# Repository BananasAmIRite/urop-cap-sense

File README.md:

# All testing code for Capacitive Sensing UROP

## Outline

- `cap_sense_lib/`: Uses the CapacitiveSensor to sense effective capacitance
- `cap_sense_basic/`: Basic Arduino sketch for capacitive sensing experiments. Replicates implementation by cap_sense_lib
- `test_square_wave/`: Testing square wave generation and receiving it using electrodes that are not touching

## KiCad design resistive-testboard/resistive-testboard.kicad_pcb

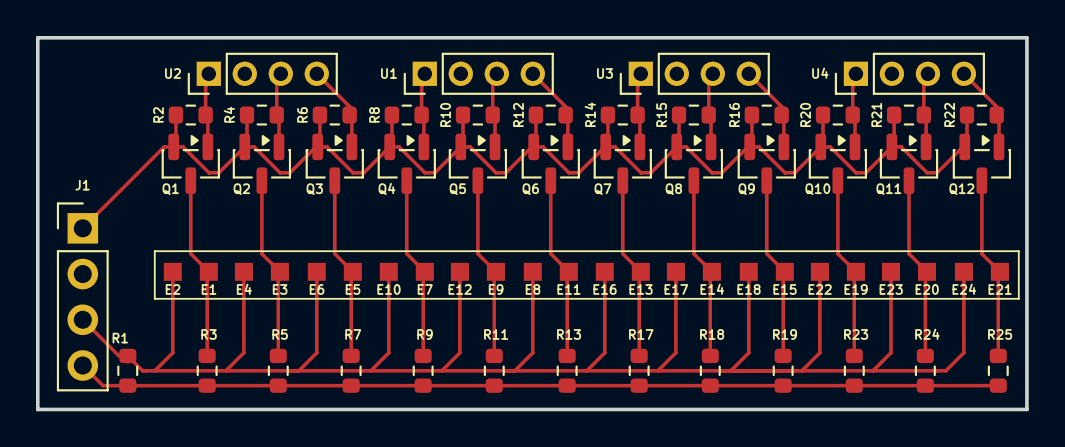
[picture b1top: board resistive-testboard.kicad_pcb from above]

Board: 2 copper layers, 55.0 x 20.6 mm, 66 parts (0 on the bottom side), 27 nets.

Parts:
E1, E2, E3, E4, E5, E6, E7, E8, E9, E10, E11, E12, E13, E14, E15, E16, E17, E18, E19, E20, E21, E22, E23, E24: Electrode
J1: Conn_01x04_Pin; PinHeader_1x04_P2.54mm_Vertical
Q1, Q2, Q3, Q4, Q5, Q6, Q7, Q8, Q9, Q10, Q11, Q12: PMOS; SOT-23
R1: 10k; R_0603_1608Metric
R2, R4, R6, R8, R10, R12, R14, R15, R16, R20, R21, R22: 10M; R_0603_1608Metric
R3, R5, R7, R9, R11, R13, R17, R18, R19, R23, R24, R25: R; R_0603_1608Metric
U1, U2, U3, U4: PinHeader_1x04_P2.00mm_Vertical

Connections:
/M1/S1/SIG_IN: Q1.1 (G), R2.2, U2.1 (R_OUT)
/M1/S2/SIG_IN: Q2.1 (G), R4.2, U2.3 (G_OUT)
/M1/S3/SIG_IN: Q3.1 (G), R6.2, U2.4 (B_OUT)
/M2/S1/SIG_IN: Q4.1 (G), R8.2, U1.1 (R_OUT)
/M2/S2/SIG_IN: Q5.1 (G), R10.2, U1.3 (G_OUT)
/M2/S3/SIG_IN: Q6.1 (G), R12.2, U1.4 (B_OUT)
/M3/S1/SIG_IN: Q7.1 (G), R14.2, U3.1 (R_OUT)
/M3/S2/SIG_IN: Q8.1 (G), R15.2, U3.3 (G_OUT)
/M3/S3/SIG_IN: Q9.1 (G), R16.2, U3.4 (B_OUT)
/M4/S1/SIG_IN: Q10.1 (G), R20.2, U4.1 (R_OUT)
/M4/S2/SIG_IN: Q11.1 (G), R21.2, U4.3 (G_OUT)
/M4/S3/SIG_IN: Q12.1 (G), R22.2, U4.4 (B_OUT)
/V_SIG: J1.1, Q1.2 (S), Q2.2 (S), Q3.2 (S), Q4.2 (S), Q5.2 (S), Q6.2 (S), Q7.2 (S), Q8.2 (S), Q9.2 (S), Q10.2 (S), Q11.2 (S), Q12.2 (S), R2.1, R4.1, R6.1, R8.1, R10.1, R12.1, R14.1, R15.1, R16.1, R20.1, R21.1, R22.1
GND: J1.4, R1.2, R3.2, R5.2, R7.2, R9.2, R11.2, R13.2, R17.2, R18.2, R19.2, R23.2, R24.2, R25.2
unnamed: E1.1 (E_1), Q1.3 (D), R3.1
unnamed: E3.1 (E_1), Q2.3 (D), R5.1
unnamed: E5.1 (E_1), Q3.3 (D), R7.1
unnamed: E7.1 (E_1), Q4.3 (D), R9.1
unnamed: E9.1 (E_1), Q5.3 (D), R11.1
unnamed: E11.1 (E_1), Q6.3 (D), R13.1
unnamed: E13.1 (E_1), Q7.3 (D), R17.1
unnamed: E14.1 (E_1), Q8.3 (D), R18.1
unnamed: E15.1 (E_1), Q9.3 (D), R19.1
unnamed: E19.1 (E_1), Q10.3 (D), R23.1
unnamed: E20.1 (E_1), Q11.3 (D), R24.1
unnamed: E21.1 (E_1), Q12.3 (D), R25.1
RX: E2.1 (E_1), E4.1 (E_1), E6.1 (E_1), E8.1 (E_1), E10.1 (E_1), E12.1 (E_1), E16.1 (E_1), E17.1 (E_1), E18.1 (E_1), E22.1 (E_1), E23.1 (E_1), E24.1 (E_1), J1.3, R1.1

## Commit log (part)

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2026-03-25 upload
2026-06-26 added circuits, shiftreg cap sense code
